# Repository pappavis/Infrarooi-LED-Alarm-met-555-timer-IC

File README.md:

### Infrarooi ligsensor
Knipperend LEDje en ligsensitief alarm, deur gebruik van 'n 555-timer skyfie.<br/>
<br/>
### CREDITS
2017.04.28 deur Michiel Erasmus uit Ellisras, Suid-Afrika.<br/>
<br/>
### VOORBEELD
100% werk in uitvoering!!<br/>
<br/>
<br/>
### Ontwerp
Die ontwerp is gemaak met KiCAD 4.0.4<br/>
<br/>
<br/>
### Komponente<br/>
1x NE555P timer IC<br/>
1x LM358P op amp IC<br/>
1x 10k potmeter<br/>
1x 200ohm weerstand<br/>
1x 10uF capacitor<br/>
1x Piezzo buzzer, nie gepolariseerd.<br/>
ens ens.<br/>
<br/>
<br/>
### Wordt vervolgd..<br/>
<br/>

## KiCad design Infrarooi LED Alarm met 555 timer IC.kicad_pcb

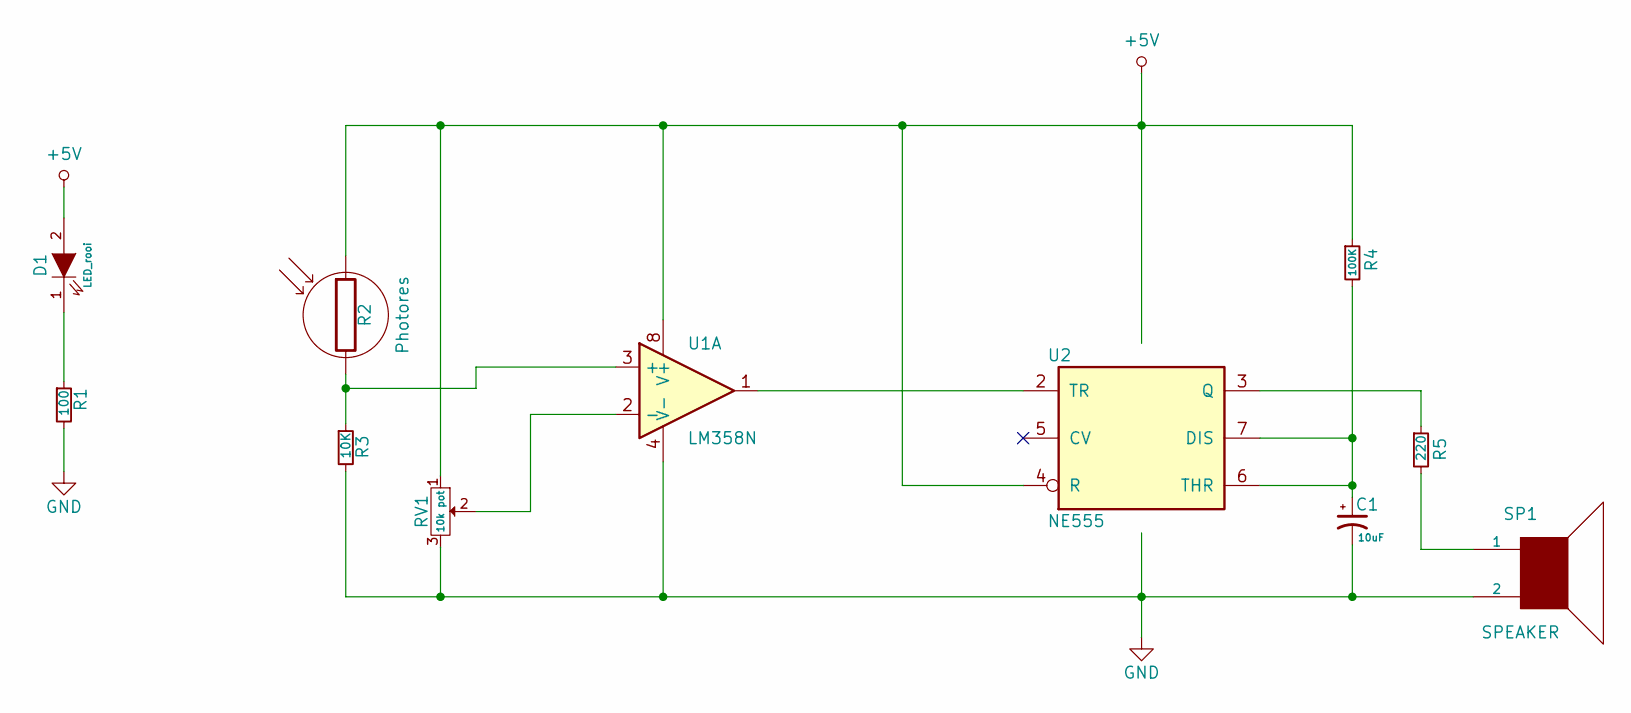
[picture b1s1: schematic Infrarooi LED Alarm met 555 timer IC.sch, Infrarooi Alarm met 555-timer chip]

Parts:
C1: 10uF; CP_Radial_D5.0mm_P2.50mm
D1: LED_rooi; led_5mm_red
R1: 100; rc05_vert
R2: Photores; D_DO-201_P5.08mm_Vertical_KathodeUp
R3: 10K; rc05_vert
R4: 100K; rc05_vert
R5: 220; rc05_vert
RV1: 10k pot; trimmer_ecp_ca9-v10
SP1: SPEAKER; MagneticBuzzer_ProSignal_ABI-009-RC
U1: LM358N; dil_8-300_socket
U2: NE555; dil_8-300_socket

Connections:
+5V: D1.2 (A), R2.1, R4.1, RV1.1, U1.8 (V+), U2.4 (R), U2.8 (VCC)
GND: C1.2, R1.2, R3.2, RV1.3, SP1.2, U1.4 (V-), U2.1 (GND)
unnamed: C1.1, R4.2, U2.6 (THR), U2.7 (DIS)
unnamed: D1.1 (K), R1.1
unnamed: R2.2, R3.1, U1.3 (+)
unnamed: R5.1, U2.3 (Q)
unnamed: R5.2, SP1.1
unnamed: RV1.2, U1.2 (-)
unnamed: U1.1, U2.2 (TR)

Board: 2 copper layers, 11 parts (0 on the bottom side), 9 nets, no tracks yet.

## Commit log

2018-04-28 :tada: Added .gitattributes & .gitignore files
2018-04-28 eerste upload
2018-06-28 CAp toevoeging

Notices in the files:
Infrarooi LED Alarm met 555 timer IC.kicad_pcb:
©2018 EasyLab4Kids
